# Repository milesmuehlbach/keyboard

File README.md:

# keyboard

A mechanical keyboard, designed by me, using [keeb's](https://keeb.hackclub.com) tutorial (for basic overview and guidance; once I knew the general direction to take each step it was mostly independent).
Mx style switches, in a slightly-larger-than 60% layout, designed with a select few extra keys I deemed important.
Additionally features a rotary encoder for volume & media playback.

I built this project because I wanted a good project to get into hardware/pcb design and all of the projects I'd previously thought of were too basic to waste the money + resources on making them real. Someone I knew had done some sort of custom keyboard, but I think it was moreso a scenario of him buying the pcb and the switches and just putting em together, etc, but I thought it was really cool to make your own keyboard so it was kind of in the back of my mind. Either way, I needed a mechanical keyboard and after realizing that it was somewhat attainable I set off to it. I'd messed with KICAD before in the past so I knew that was the way to go, and I was having trouble running fusion on my laptop so onshape it is! 

I'm using [RMK](https://rmk.rs/docs/user_guide/guide_overview) for firmware, located in `firmware/`

I built the PCB in KICAD, which is in `pcb/`

[Onshape Assembly](https://cad.onshape.com/documents/6ce0951954889885430f0539/w/e429278c0dacc60c66f83916/e/a9e79258290a2b0808a28da1?renderMode=0&uiState=6ad5325657fff16aba3cf861)
> you can also find step files and other various models in `3dmodels/`

## Firmware setup
Make sure the rust toolchain is installed. Install the compilation target for your microcontroller; in our case it's a pi pico 1 so it'll be `thumbv6m-none-eabi`

Install rmk deps:
```sh
cargo install rmkit
cargo install flip-link cargo-make
```
The firmware is already configured for this specific board layout and pinout, etc. 

Build firmware with 
```sh
cargo make uf2 --release
```
You'll find the compiled uf2 (which can be loaded normally to the pi pico) at `target/thumbv6m-none-eabi/release/*.uf2`

**BOM:** [BOM.csv](BOM.csv), or view it below:

## Bill of Materials

| Item | Price |
| --- | ---: |
| [PI Pico Starter Kit](https://www.amazon.com/KEYESTUDIO-Raspberry-Starter-Headers-Breadboard/dp/B0861WJ2DD) | $9.45 |
| [PCB (jlcPCB)](https://jlcpcb.com) | $23.30 |
| [EC11 Rotary Encoder](https://keeb.io/products/rotary-encoder-ec11) | $1.99 |
| [Through-hole 1N4148 Diodes (100-pack)](https://keeb.io/products/1n4148-diodes) | $2.99 |
| [MX Plate Mount Stabilizers](https://www.amazon.com/DUROCK-Stabilizer-Innovative-Pre-clipped-Stabilizers/dp/B0CTHT34MJ) | $9.99 |
| [DSA Keycap set](https://www.amazon.com/YMDK-Profile-Keyset-Mechanical-Keyboard/dp/B07GP29DQF) | $22.50 |
| [Cherry MX Tactile Brown RGB GEN 2 switches (2 packs)](https://www.microcenter.com/product/708639/cherry-mx-tactile-brown-rgb-gen-2-key-switches) | $39.98 |
| [M3 brass heat-set inserts (3 mm long; 50-pack)](https://www.adafruit.com/product/4256) | $5.95 |
| **Subtotal** | **$116.15** |

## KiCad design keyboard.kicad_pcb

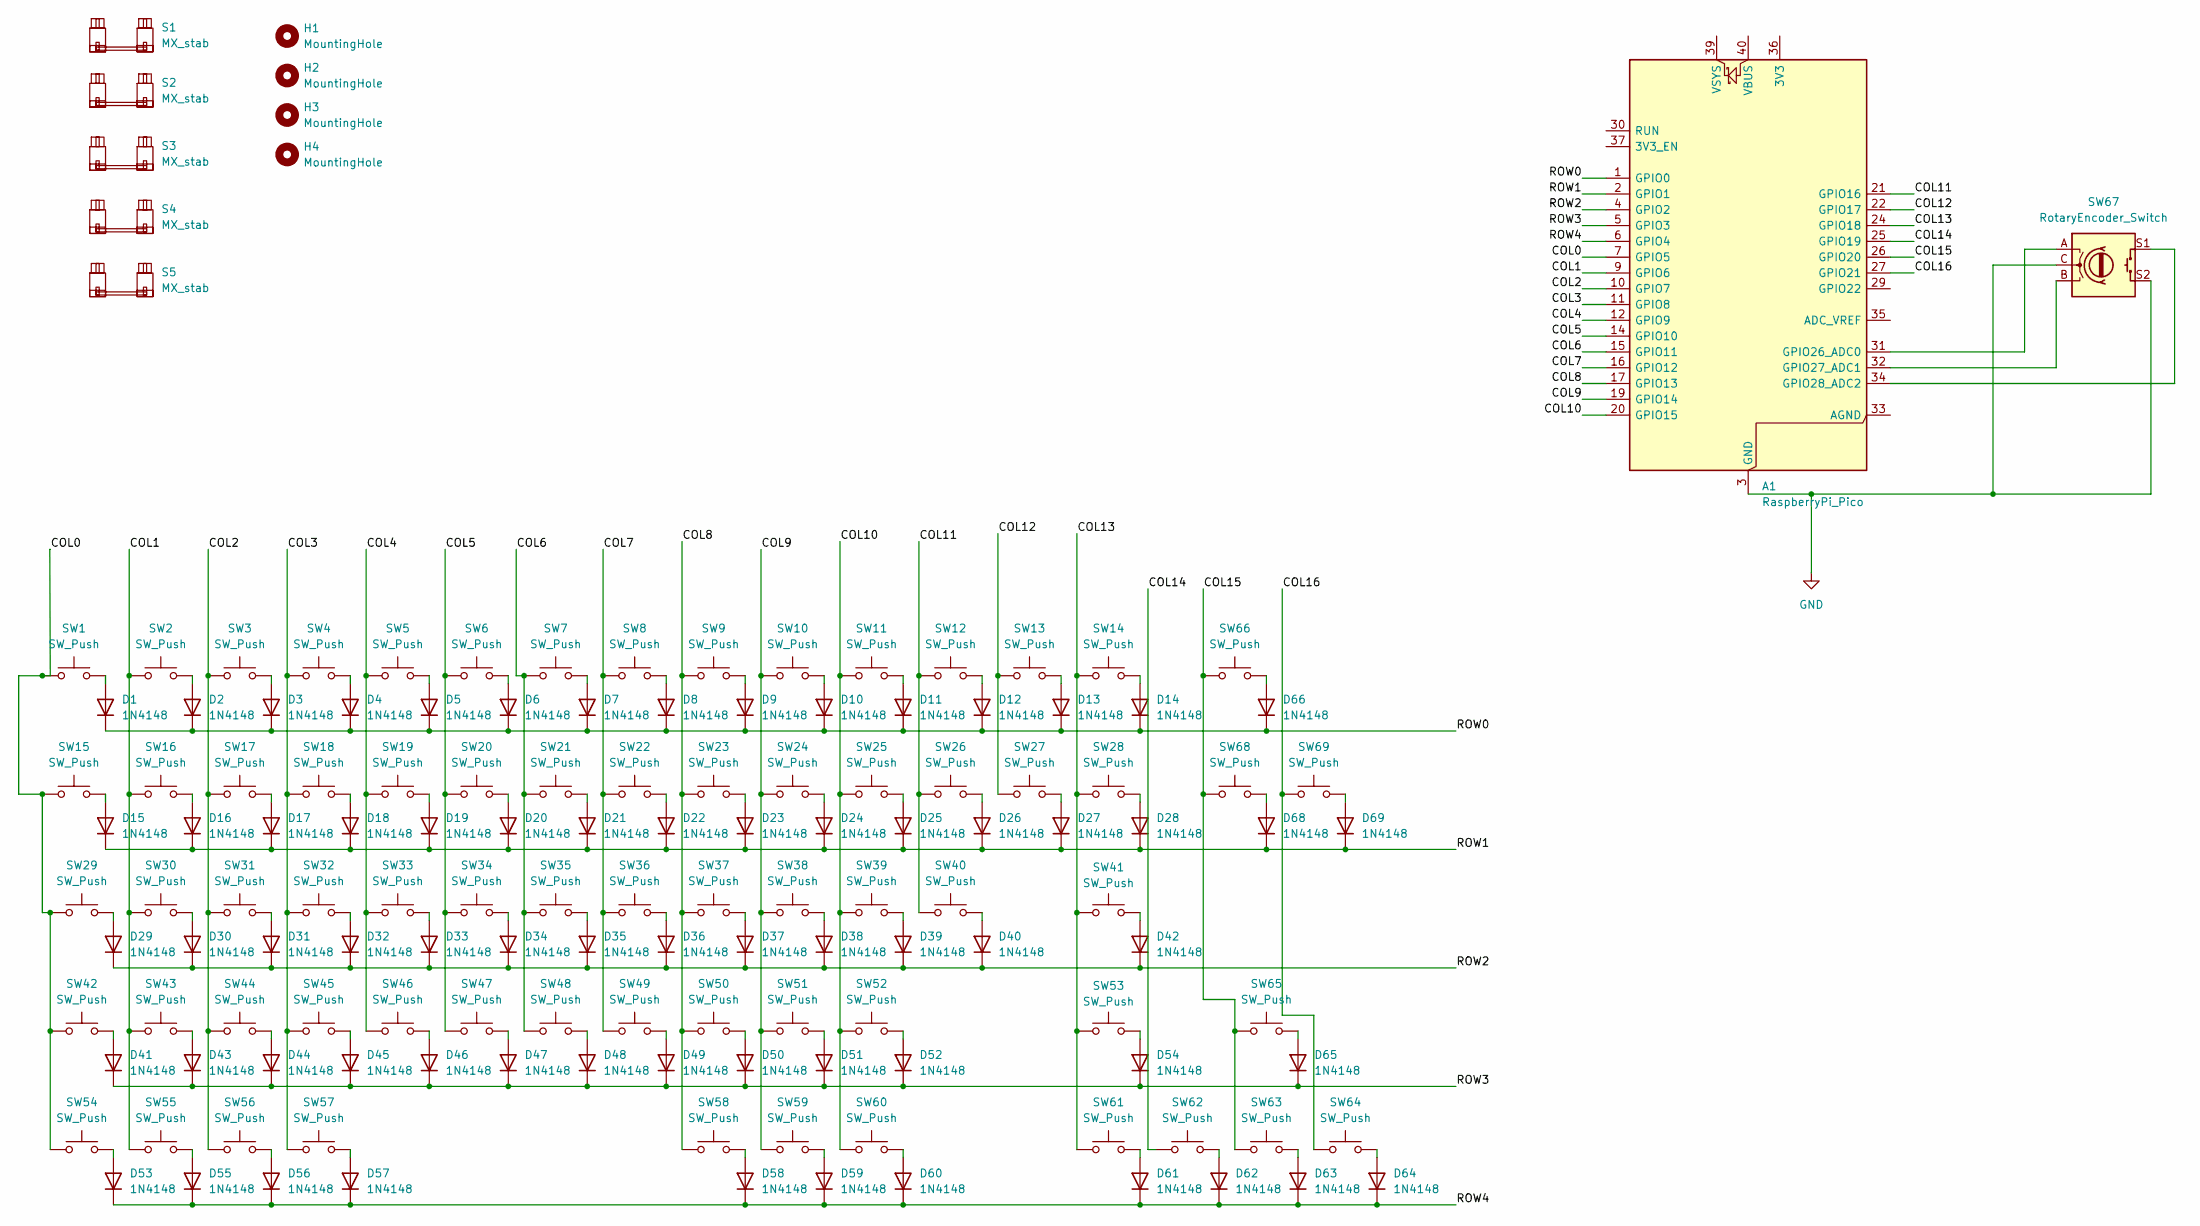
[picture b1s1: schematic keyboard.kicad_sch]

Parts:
A1: RaspberryPi_Pico; RaspberryPi_Pico_Common_THT
D1, D2, D3, D4, D5, D6, D7, D8, D9, D10, D11, D12, D13, D14, D15, D16, D17, D18, D19, D20, D21, D22, D23, D24, D25, D26, D27, D28, D29, D30, D31, D32, D33, D34, D35, D36, D37, D38, D39, D40, D41, D42, D43, D44, D45, D46, D47, D48, D49, D50, D51, D52, D53, D54, D55, D56, D57, D58, D59, D60, D61, D62, D63, D64, D65, D66, D68, D69: 1N4148; D_DO-35_SOD27_P7.62mm_Horizontal
H1, H2, H3, H4: MountingHole; MountingHole_2.2mm_M2
S1, S2, S3, S4: MX_stab; STAB_MX_2u
S5: MX_stab; STAB_MX_6.25u
SW1, SW2, SW3, SW4, SW5, SW6, SW7, SW8, SW9, SW10, SW11, SW12, SW13, SW14, SW16, SW17, SW18, SW19, SW20, SW21, SW22, SW23, SW24, SW25, SW26, SW27, SW30, SW31, SW32, SW33, SW34, SW35, SW36, SW37, SW38, SW39, SW40, SW41, SW42, SW43, SW44, SW45, SW46, SW47, SW48, SW49, SW50, SW51, SW52, SW53, SW57, SW62, SW63, SW64, SW65, SW66, SW68, SW69: SW_Push; SW_MX_1u
SW15, SW28: SW_Push; SW_MX_1.5u
SW29: SW_Push; SW_MX_1.75u
SW54, SW55, SW56, SW58, SW59, SW60, SW61: SW_Push; SW_MX_1.25u
SW67: RotaryEncoder_Switch; RotaryEncoder_Alps_EC11E-Switch_Vertical_H20mm_CircularMoun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

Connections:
/COL0: A1.7 (GPIO5), SW1.1, SW15.1, SW29.1, SW42.1, SW54.1
/COL1: A1.9 (GPIO6), SW2.1, SW16.1, SW30.1, SW43.1, SW55.1
/COL2: A1.10 (GPIO7), SW3.1, SW17.1, SW31.1, SW44.1, SW56.1
/COL3: A1.11 (GPIO8), SW4.1, SW18.1, SW32.1, SW45.1, SW57.1
/COL4: A1.12 (GPIO9), SW5.1, SW19.1, SW33.1, SW46.1
/COL5: A1.14 (GPIO10), SW6.1, SW20.1, SW34.1, SW47.1
/COL6: A1.15 (GPIO11), SW7.1, SW21.1, SW35.1, SW48.1
/COL7: A1.16 (GPIO12), SW8.1, SW22.1, SW36.1, SW49.1
/COL8: A1.17 (GPIO13), SW9.1, SW23.1, SW37.1, SW50.1, SW58.1
/COL9: A1.19 (GPIO14), SW10.1, SW24.1, SW38.1, SW51.1, SW59.1
/COL10: A1.20 (GPIO15), SW11.1, SW25.1, SW39.1, SW52.1, SW60.1
/COL11: A1.21 (GPIO16), SW12.1, SW26.1, SW40.1
/COL12: A1.22 (GPIO17), SW13.1, SW27.1
/COL13: A1.24 (GPIO18), SW14.1, SW28.1, SW41.1, SW53.1, SW61.1
/COL14: A1.25 (GPIO19), SW62.1
/COL15: A1.26 (GPIO20), SW63.1, SW65.1, SW66.1, SW68.1
/COL16: A1.27 (GPIO21), SW64.1, SW69.1
/ROW0: A1.1 (GPIO0), D1.1 (K), D2.1 (K), D3.1 (K), D4.1 (K), D5.1 (K), D6.1 (K), D7.1 (K), D8.1 (K), D9.1 (K), D10.1 (K), D11.1 (K), D12.1 (K), D13.1 (K), D14.1 (K), D66.1 (K)
/ROW1: A1.2 (GPIO1), D15.1 (K), D16.1 (K), D17.1 (K), D18.1 (K), D19.1 (K), D20.1 (K), D21.1 (K), D22.1 (K), D23.1 (K), D24.1 (K), D25.1 (K), D26.1 (K), D27.1 (K), D28.1 (K), D68.1 (K), D69.1 (K)
/ROW2: A1.4 (GPIO2), D29.1 (K), D30.1 (K), D31.1 (K), D32.1 (K), D33.1 (K), D34.1 (K), D35.1 (K), D36.1 (K), D37.1 (K), D38.1 (K), D39.1 (K), D40.1 (K), D42.1 (K)
/ROW3: A1.5 (GPIO3), D41.1 (K), D43.1 (K), D44.1 (K), D45.1 (K), D46.1 (K), D47.1 (K), D48.1 (K), D49.1 (K), D50.1 (K), D51.1 (K), D52.1 (K), D54.1 (K), D65.1 (K)
/ROW4: A1.6 (GPIO4), D53.1 (K), D55.1 (K), D56.1 (K), D57.1 (K), D58.1 (K), D59.1 (K), D60.1 (K), D61.1 (K), D62.1 (K), D63.1 (K), D64.1 (K)
GND: A1.3 (GND), A1.8 (GND), A1.13 (GND), A1.18 (GND), A1.23 (GND), A1.28 (GND), A1.38 (GND), SW67.C, SW67.S2
unnamed: A1.31 (GPIO26_ADC0), SW67.A
unnamed: A1.32 (GPIO27_ADC1), SW67.B
unnamed: A1.34 (GPIO28_ADC2), SW67.S1
unnamed: D1.2 (A), SW1.2
unnamed: D2.2 (A), SW2.2
unnamed: D3.2 (A), SW3.2
unnamed: D4.2 (A), SW4.2
unnamed: D5.2 (A), SW5.2
unnamed: D6.2 (A), SW6.2
unnamed: D7.2 (A), SW7.2
unnamed: D8.2 (A), SW8.2
unnamed: D9.2 (A), SW9.2
unnamed: D10.2 (A), SW10.2
unnamed: D11.2 (A), SW11.2
unnamed: D12.2 (A), SW12.2
unnamed: D13.2 (A), SW13.2
unnamed: D14.2 (A), SW14.2
unnamed: D15.2 (A), SW15.2
unnamed: D16.2 (A), SW16.2
unnamed: D17.2 (A), SW17.2
unnamed: D18.2 (A), SW18.2
unnamed: D19.2 (A), SW19.2
unnamed: D20.2 (A), SW20.2
unnamed: D21.2 (A), SW21.2
unnamed: D22.2 (A), SW22.2
unnamed: D23.2 (A), SW23.2
unnamed: D24.2 (A), SW24.2
unnamed: D25.2 (A), SW25.2
unnamed: D26.2 (A), SW26.2
unnamed: D27.2 (A), SW27.2
unnamed: D28.2 (A), SW28.2
unnamed: D29.2 (A), SW29.2
unnamed: D30.2 (A), SW30.2
unnamed: D31.2 (A), SW31.2
unnamed: D32.2 (A), SW32.2
unnamed: D33.2 (A), SW33.2
unnamed: D34.2 (A), SW34.2
unnamed: D35.2 (A), SW35.2
unnamed: D36.2 (A), SW36.2
unnamed: D37.2 (A), SW37.2
unnamed: D38.2 (A), SW38.2
unnamed: D39.2 (A), SW39.2
unnamed: D40.2 (A), SW40.2
unnamed: D41.2 (A), SW42.2
unnamed: D42.2 (A), SW41.2
unnamed: D43.2 (A), SW43.2
unnamed: D44.2 (A), SW44.2
unnamed: D45.2 (A), SW45.2
unnamed: D46.2 (A), SW46.2
unnamed: D47.2 (A), SW47.2
unnamed: D48.2 (A), SW48.2
unnamed: D49.2 (A), SW49.2
unnamed: D50.2 (A), SW50.2
unnamed: D51.2 (A), SW51.2
unnamed: D52.2 (A), SW52.2
unnamed: D53.2 (A), SW54.2
unnamed: D54.2 (A), SW53.2
unnamed: D55.2 (A), SW55.2
unnamed: D56.2 (A), SW56.2
unnamed: D57.2 (A), SW57.2
unnamed: D58.2 (A), SW58.2
unnamed: D59.2 (A), SW59.2
unnamed: D60.2 (A), SW60.2
unnamed: D61.2 (A), SW61.2
unnamed: D62.2 (A), SW62.2
unnamed: D63.2 (A), SW63.2
unnamed: D64.2 (A), SW64.2
unnamed: D65.2 (A), SW65.2
unnamed: D66.2 (A), SW66.2
unnamed: D68.2 (A), SW68.2
unnamed: D69.2 (A), SW69.2

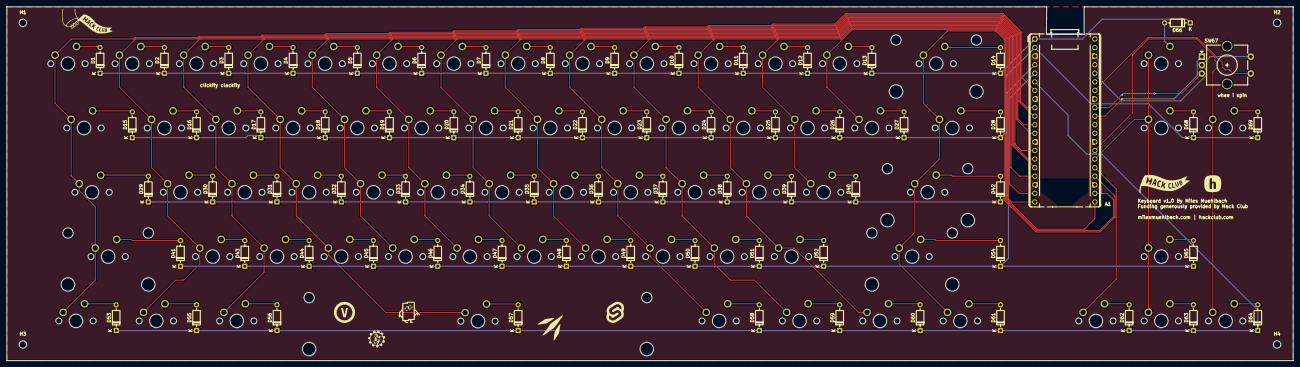
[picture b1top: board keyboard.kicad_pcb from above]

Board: 2 copper layers, 381.0 x 104.8 mm, 147 parts (0 on the bottom side), 94 nets.
